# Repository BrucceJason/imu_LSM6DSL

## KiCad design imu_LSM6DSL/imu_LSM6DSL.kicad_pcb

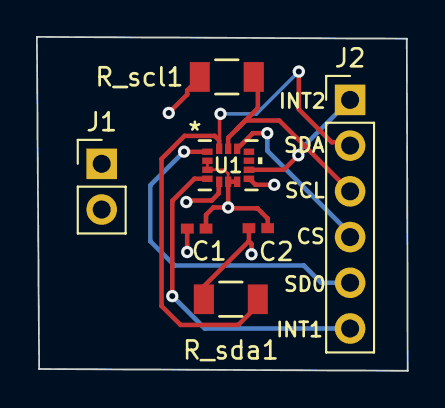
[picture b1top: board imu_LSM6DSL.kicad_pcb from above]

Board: 4 copper layers, 20.6 x 18.6 mm, 7 parts (0 on the bottom side), 9 nets.

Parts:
C1, C2: 100nF; CAP_GRM155_MUR
J1: Conn_01x02; PinHeader_1x02_P2.54mm_Vertical
J2: Conn_01x06; PinHeader_1x06_P2.54mm_Vertical
R_scl1: 1k; 1206_PAN
R_sda1: 1k; 1206_PAN
U1: LSM6DSLTR; QFN_6DSLTR_STM

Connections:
/CS: J2.4, U1.12 (CS)
/INT1: J2.6, U1.4 (INT1)
/INT2: J2.1, U1.9 (INT2)
/SCL: J2.3, R_scl1.2, U1.13 (SCL)
/SDA: J2.2, R_sda1.2, U1.14 (SDA)
/SDO/SA0: J2.5, U1.1 (SDO/SA0)
GND: C1.2, C2.2, J1.2, U1.2 (SDX), U1.3 (SCX), U1.6 (GND), U1.7 (GND)
unnamed: C1.1, U1.8 (VDD)
VDDIO: C2.1, J1.1, R_scl1.1, R_sda1.1, U1.5 (VDDIO)

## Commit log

2024-05-14 Final version
2024-05-25 via change
